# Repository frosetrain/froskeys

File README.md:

# Froskeys

[Demo video](https://www.youtube.com/watch?v=2AYCUWPBNlQ)

A 9-key macropad that I created for my own use-cases. I wanted some more keys next to my keyboard to do things like push-to-talk and other macros. Since my mouse is on the right of my laptop, my macropad shall sit on the left of my laptop.

There is a column of keys on the right of the macropad, to easily press with my pinky while my left hand is on WASD.

There is a diagonal cutout on the bottom left, where I can rest my hand more easily.

## Keys

- Control+Z (undo) and Control+Y (redo)
- Control+C (copy) and Control+V (paste), the only two keys I need
- Control+D (duplicate)
- F2 (rename)
- Play/pause
- Push-to-talk
- `fastfetch`

## Schematic

## PCB

## Case

| Top                         | Bottom                            |
| --------------------------- | --------------------------------- |
|  |  |

**CAD render**

Section analysis was a very useful feature

## BOM

### JLCPCB

- PCB

### 3D Printed

- Case

### Components

- 1 × Seeed Studio XIAO RP2040
- 9 × 1N4148 Diode
- 1 × EC11 Rotary Encoder
- 1 × 0.91″ I²C OLED Display
- 9 × White XDA Profile PBT Keycaps
- 9 × SK6812 MINI-E LED
- 4 × M3×16mm screw
- 4 × M3×5mm×4mm heatset insert
- 9 × Gateron Baby Kangaroo 2.0

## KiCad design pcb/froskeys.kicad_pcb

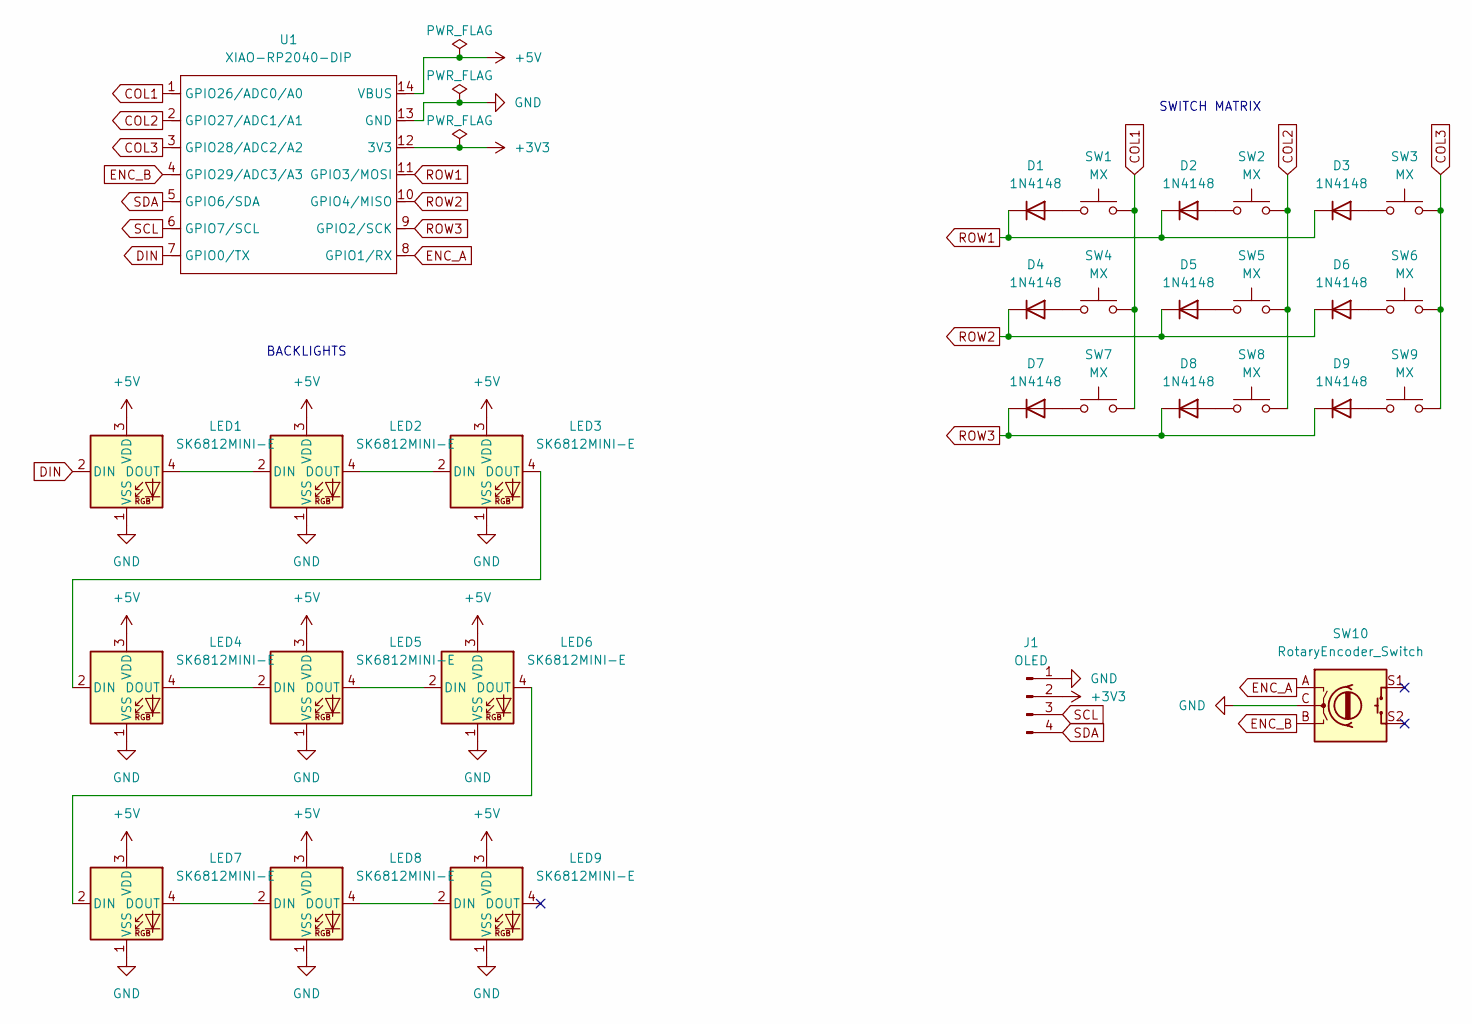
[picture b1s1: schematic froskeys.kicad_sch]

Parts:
D1, D2, D3, D4, D5, D6, D7, D8, D9: 1N4148; D_DO-35_SOD27_P7.62mm_Horizontal
J1: OLED; SSD1306-0.91-OLED-4pin-128x32
LED1, LED2, LED3, LED4, LED5, LED6, LED7, LED8, LED9: SK6812MINI-E; MX_SK6812MINI-E_GOOD
SW1, SW2, SW3, SW4, SW5, SW6, SW7, SW8, SW9: MX; MX-Solderable-1U
SW10: RotaryEncoder_Switch; RotaryEncoder_Alps_EC11E-Switch_Vertical_H20mm
U1: XIAO-RP2040-DIP

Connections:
+3V3: J1.2, U1.12 (3V3)
+5V: LED1.3 (VDD), LED2.3 (VDD), LED3.3 (VDD), LED4.3 (VDD), LED5.3 (VDD), LED6.3 (VDD), LED7.3 (VDD), LED8.3 (VDD), LED9.3 (VDD), U1.14 (VBUS)
COL1: SW1.2, SW4.2, SW7.2, U1.1 (GPIO26/ADC0/A0)
COL2: SW2.2, SW5.2, SW8.2, U1.2 (GPIO27/ADC1/A1)
COL3: SW3.2, SW6.2, SW9.2, U1.3 (GPIO28/ADC2/A2)
DIN: LED1.2 (DIN), U1.7 (GPIO0/TX)
ENC_A: SW10.A, U1.8 (GPIO1/RX)
ENC_B: SW10.B, U1.4 (GPIO29/ADC3/A3)
GND: J1.1, LED1.1 (VSS), LED2.1 (VSS), LED3.1 (VSS), LED4.1 (VSS), LED5.1 (VSS), LED6.1 (VSS), LED7.1 (VSS), LED8.1 (VSS), LED9.1 (VSS), SW10.C, U1.13 (GND)
unnamed: D1.2 (A), SW1.1
unnamed: D2.2 (A), SW2.1
unnamed: D3.2 (A), SW3.1
unnamed: D4.2 (A), SW4.1
unnamed: D5.2 (A), SW5.1
unnamed: D6.2 (A), SW6.1
unnamed: D7.2 (A), SW7.1
unnamed: D8.2 (A), SW8.1
unnamed: D9.2 (A), SW9.1
unnamed: LED1.4 (DOUT), LED2.2 (DIN)
unnamed: LED2.4 (DOUT), LED3.2 (DIN)
unnamed: LED3.4 (DOUT), LED4.2 (DIN)
unnamed: LED4.4 (DOUT), LED5.2 (DIN)
unnamed: LED5.4 (DOUT), LED6.2 (DIN)
unnamed: LED6.4 (DOUT), LED7.2 (DIN)
unnamed: LED7.4 (DOUT), LED8.2 (DIN)
unnamed: LED8.4 (DOUT), LED9.2 (DIN)
ROW1: D1.1 (K), D2.1 (K), D3.1 (K), U1.11 (GPIO3/MOSI)
ROW2: D4.1 (K), D5.1 (K), D6.1 (K), U1.10 (GPIO4/MISO)
ROW3: D7.1 (K), D8.1 (K), D9.1 (K), U1.9 (GPIO2/SCK)
SCL: J1.3, U1.6 (GPIO7/SCL)
SDA: J1.4, U1.5 (GPIO6/SDA)

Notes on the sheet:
SWITCH MATRIX
BACKLIGHTS

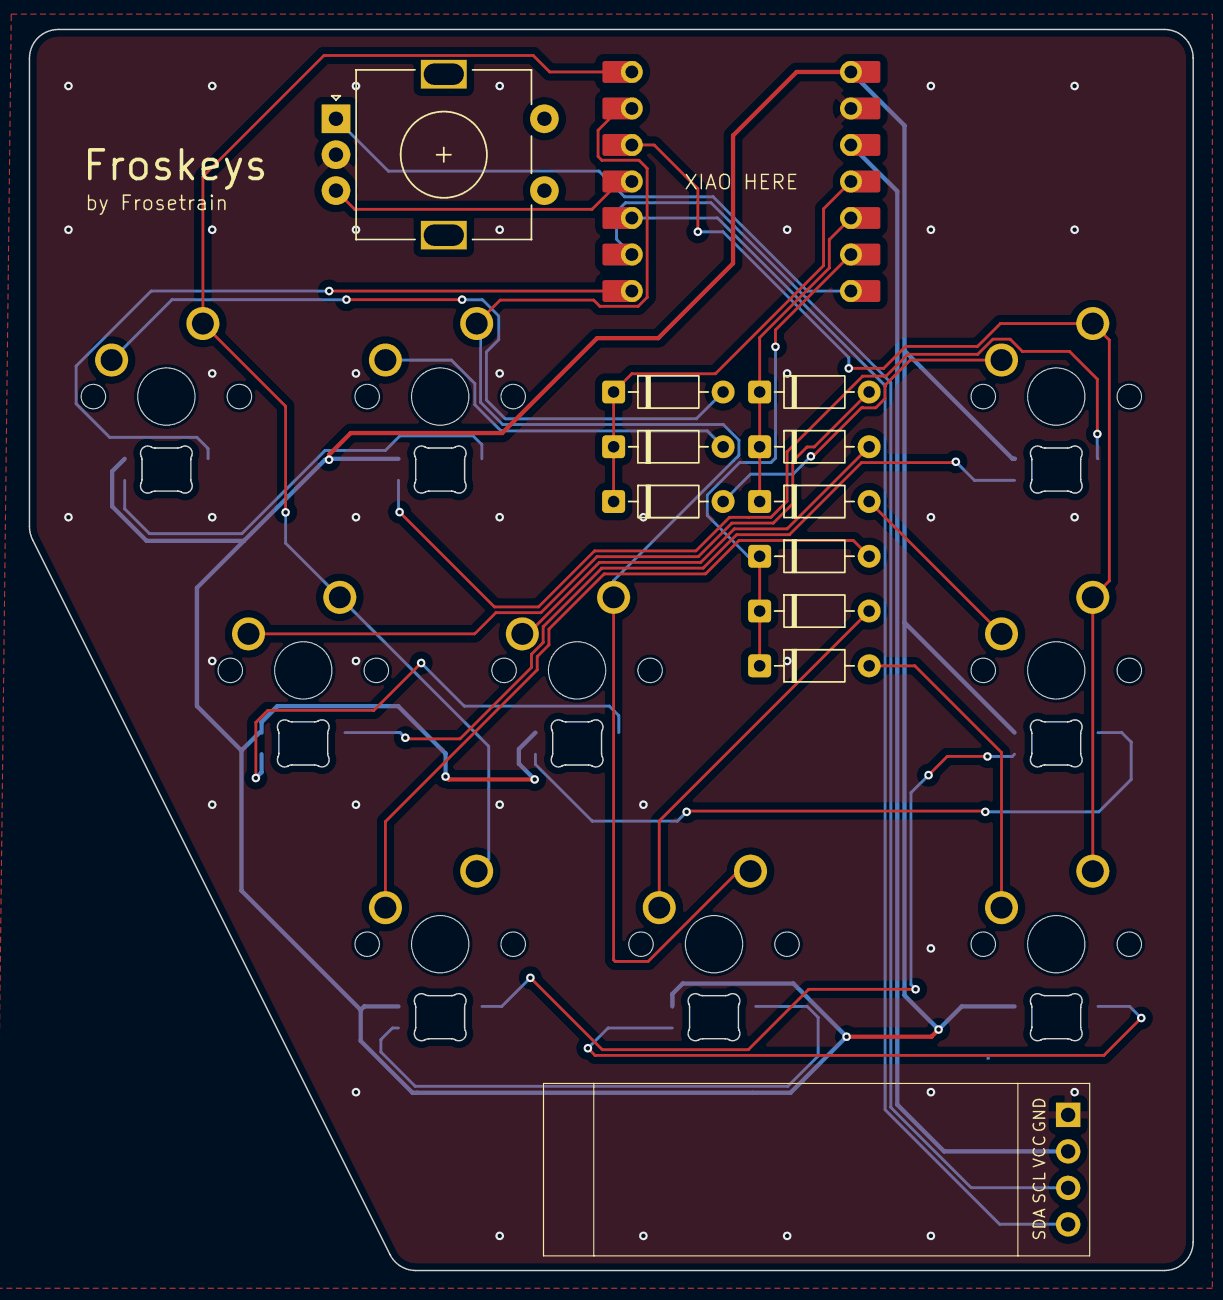
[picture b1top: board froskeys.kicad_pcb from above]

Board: 2 copper layers, 81.0 x 86.3 mm, 32 parts (1 on the bottom side), 31 nets.

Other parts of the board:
KICAD: KiCad-Logo2_6mm_Copper
OSHW: OSHW-Logo_7.5x8mm_Copper

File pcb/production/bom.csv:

Designator,Footprint,Quantity,Value,LCSC Part #
"D1, D2, D3, D4, D5, D6, D7, D8, D9",D_DO-35_SOD27_P7.62mm_Horizontal,9,1N4148,
J1,SSD1306-0.91-OLED-4pin-128x32,1,OLED,
"LED1, LED2, LED3, LED4, LED5, LED6, LED7, LED8, LED9",MX_SK6812MINI-E_GOOD,9,SK6812MINI-E,
"SW1, SW2, SW3, SW4, SW5, SW6, SW7, SW8, SW9",MX-Solderable-1U,9,MX,
SW10,RotaryEncoder_Alps_EC11E-Switch_Vertical_H20mm,1,RotaryEncoder_Switch,
U1,XIAO-RP2040-DIP,1,XIAO-RP2040-DIP,

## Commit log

2025-06-23 Seems cool
2025-06-23 Optimise
2025-06-23 Is this good
2025-06-23 Remove OLED symbol
2025-06-26 Switch to SK6812MINI-E backlighting
2025-07-07 whah
2025-07-07 Is this real
2025-07-07 Create LICENSE
2025-07-07 Add gerbers
2025-07-07 Add readme
2025-08-16 Convert to Grounded project
2025-09-25 Hmm this is interesting
2025-09-26 Mm fix encoder
2025-09-26 Switch to SEEED pin numbers
2025-09-26 Change encoder direction and add SK6812 test
2025-09-28 Change SK6812 pin order
2025-09-28 Oops add stitching vias
2026-03-15 embed no
